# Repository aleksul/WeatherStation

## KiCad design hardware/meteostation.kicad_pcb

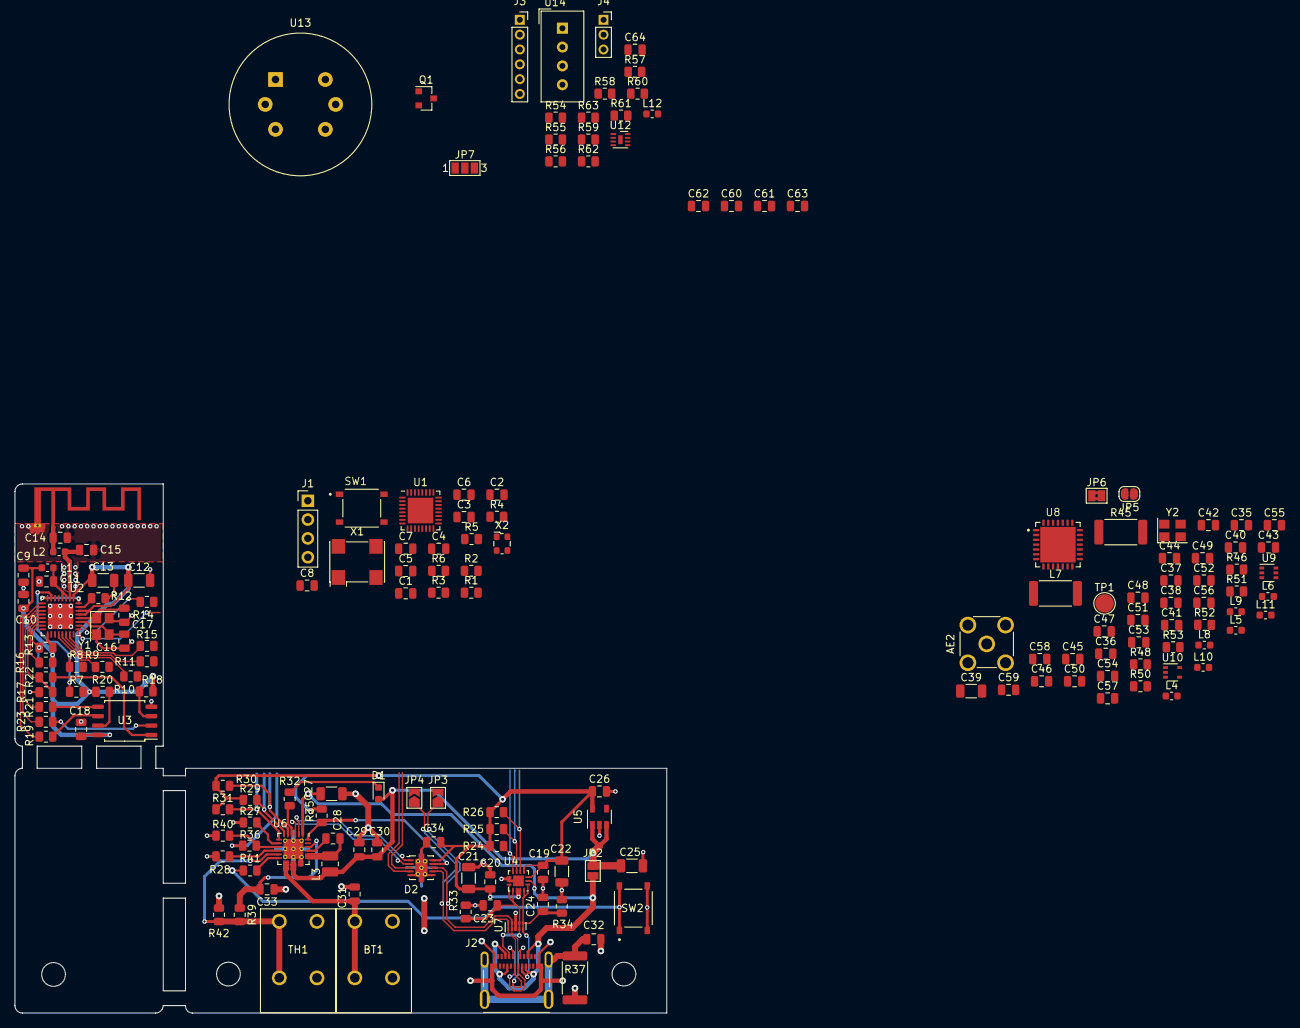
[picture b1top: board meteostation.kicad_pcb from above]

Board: 2 copper layers, 87.9 x 71.3 mm, 172 parts (1 on the bottom side), 115 nets.

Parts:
AE1: Antenna_Chip; Texas_SWRA117D_2.4GHz_Right
AE2: SMA Antenna; SMA_Molex_73251-2200_Horizontal
BT1: Li-Po Battery; DG142R-5.08-02P-14
C1, C2, C5, C6, C7, C8, C10, C11, C18, C19, C20, C32, C34, C40, C41, C42, C54, C55, C64: 100nF; C_0805_2012Metric
C3, C4, C46, C47, C48: 15pF; C_0805_2012Metric
C9, C26, C29, C30, C61, C62, C63: 10uF; C_0805_2012Metric
C12, C13, C21, C22, C25, C27, C39: 1uF; C_1206_3216Metric
C14: 2.4pF; C_0805_2012Metric
C15: 3.0pF; C_0805_2012Metric
C16, C17, C44, C50: 7pF; C_0805_2012Metric
C23, C24: 470pF; C_0805_2012Metric
C28, C43: 47nF; C_0805_2012Metric
C31: 10uF 25V; C_0805_2012Metric
C33, C60: 4.7uF; C_0805_2012Metric
C35, C36, C52, C53, C56: 47pF; C_0805_2012Metric
C37, C38: 2.7pF; C_0805_2012Metric
C45: 18pF; C_0805_2012Metric
C49, C57, C58: 6.8pF; C_0805_2012Metric
C51: 10nF; C_0805_2012Metric
C59: 1nF; C_0805_2012Metric
D1: LED; LED_0603_1608Metric
D2: TS3USB221DCDR; VSON-10-1EP_3x3mm_P0.5mm_EP1.65x2.4mm_ThermalVias
J1: PROG_Conn; PinHeader_1x04_P2.54mm_Vertical
J2: 105450-0101
J3: PM_Sensor; PinSocket_1x06_P2.00mm_Vertical
J4: Anemometer; PinSocket_1x03_P2.00mm_Vertical
JP1: Jumper_PROG; SolderJumper-2_P1.3mm_Open_TrianglePad1.0x1.5mm
JP2: Jumper; SolderJumper-2_P1.3mm_Open_Pad1.0x1.5mm
JP3, JP4: Jumper; SolderJumper-2_P1.3mm_Open_TrianglePad1.0x1.5mm
JP5: Jumper; SolderJumper-2_P1.3mm_Open_RoundedPad1.0x1.5mm
JP6: Jumper; SolderJumper-2_P1.3mm_Bridged2Bar_Pad1.0x1.5mm
JP7: Jumper; SolderJumper-3_P1.3mm_Open_Pad1.0x1.5mm_NumberLabels
L1: 4.3nH; L_0603_1608Metric
L2, L6: 2.2nH; L_0603_1608Metric
L3: 2.2uH; L_1008_2520Metric
L4, L5: 18nH; L_0603_1608Metric
L7: 0R; R_2512_6332Metric
L8, L9, L11: 12nH; L_0603_1608Metric
L10: 33nH; L_0603_1608Metric
L12: 1uH; L_0603_1608Metric
Q1: SI2302; SOT-23
R1, R2, R3, R5, R7, R13, R16, R17, R18, R20, R27, R35, R40, R46, R57, R59, R61, R62, R63: 10K; R_0805_2012Metric
R4, R6, R8, R9, R10, R11, R14, R15, R19, R21, R22, R23, R36, R48, R50, R51, R52, R56, R60: 100R; R_0805_2012Metric
R12: 12K ±1%; R_0805_2012Metric
R24, R25, R26, R29, R30, R31, R41, R54, R55: 4K7; R_0805_2012Metric
R28: 200R; R_0805_2012Metric
R32: 2K2; R_0805_2012Metric
R33, R34, R58: 5K1; R_0805_2012Metric
R37: 330R; R_2512_6332Metric
R39: 5K23; R_0805_2012Metric
R42: 30K1; R_0805_2012Metric
R45: 0R; R_2512_6332Metric
R53: 1K; R_0805_2012Metric
SW1: RESET_BTN; SW_TS-1187A-B-A-B
SW2: Button; SW_TS-1187A-B-A-B
TH1: Thermistor 10K; DG142R-5.08-02P-14
TP1: TestPoint; TestPoint_Pad_D2.5mm
U1: STM32L432KBUx; QFN-32-1EP_5x5mm_P0.5mm_EP3.45x3.45mm
U2: ESP8266EX; QFN-32-1EP_5x5mm_P0.5mm_EP3.45x3.45mm
U3: AT25SF081-SHD-T; SOIC-8_5.23x5.23mm_P1.27mm
U4: FUSB302BMPX; WQFN-14-1EP_2.5x2.5mm_P0.5mm_EP1.45x1.45mm
U5: TLV75533PDBV; SOT-23-5
U6: BQ25895RTW; Texas_S-PWQFN-N24_EP2.7x2.7mm_ThermalVias
U7: TPD4E02B04DQA; USON-10_2.5x1.0mm_P0.5mm
U8: SX1278IMLTRT; QFN65P600X600X100-29N
U9: TPAS179-92LF; SOT-363_SC-70-6
U10: MC74VHC1G14; SOT-353_SC-70-5
U12: HP203B; DFN-8-1EP_2x2mm_P0.5mm_EP0.6x1.2mm
U13: MQ-2; MQ-6
U14: DHT11; Aosong_DHT11_5.5x12.0_P2.54mm
X1: YSO110TR_8MHz_10ppm; Oscillator_SMD_SeikoEpson_SG8002CA-4Pin_7.0x5.0mm
X2: YSO120TK_32.768KHz_10ppm; Oscillator_SMD_ECS_2520MV-xxx-xx-4Pin_2.5x2.0mm
Y1: YSX321SL_26MHz_10ppm; Crystal_SMD_3225-4Pin_3.2x2.5mm
Y2: YSX321SL_32.0MHz_10ppm; Crystal_SMD_3225-4Pin_3.2x2.5mm

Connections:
+3V3: C1.1, C2.1, C6.1, C7.1, C8.1, C9.1, C10.1, C12.1, C13.1, C18.1, C19.1, C20.1, C21.1, C22.1, C26.1, C34.1, C39.1, C40.1, C41.1, C42.1, C43.1, C60.1, C64.1, D2.10, JP7.3, L1.1, R1.1, R2.1, R3.1, R7.2, R13.1, R16.1, R18.2, R20.2, R24.2, R25.2, R26.2, R29.2, R30.2, R31.2, R35.1, R46.1, R54.1, R55.1, R59.1, R62.1, R63.1, U1.1, U1.5, U1.17, U2.1, U2.11, U2.17, U2.29, U2.30, U3.8, U4.3, U4.4, U4.12, U4.13, U5.5, U8.3, U8.14, U8.24, U10.5, U12.3, U12.8, U13.4, U13.6, U14.1, X1.4, X2.4
+5V: C61.1, C62.1, J3.1, JP7.1, U13.2
/Anemometer: J4.3, U1.10
/BOOT0: R5.1, U1.31
/BQ25895_INT: R31.1, U1.27, U6.7
/Charge: R36.2, U1.15
/DHT11: R59.2, U1.11, U14.2
/ESP8266/CHIP_PU: R7.1, R8.1, U2.7
/ESP8266/HSPI_CLK: R19.1, U2.9
/ESP8266/HSPI_CS: R17.2, R22.2, U2.13
/ESP8266/HSPI_MISO: R23.1, U2.10
/ESP8266/HSPI_MOSI: R21.1, U2.12
/ESP8266/RX: R4.1, U2.25
/ESP-LoRa_CS: R9.1, R48.2, U1.14
/ESP_Disable-RF_Mod: JP5.2, R8.2, U1.3
/Enable_5V: R56.2, U1.18
/Enable_MQ2: R60.2, U1.25
/FUSB302_INT: R26.1, U1.26, U4.5
/HSE: C3.1, U1.6, X1.3
/LSE: C4.1, U1.2, X2.3
/MQ2: R58.1, U1.13, U13.1, U13.3
/Power and USB/CC1: C23.1, J2.A5, R33.1, U4.10, U4.11, U7.4, U7.7
/Power and USB/CC2: C24.1, J2.B5, R34.1, U4.1, U4.14, U7.5, U7.6
/Power and USB/ControlSelect: D2.9, R35.2, U6.24
/Power and USB/D+: D2.8, J2.A6, J2.B6, JP3.1, U7.2, U7.9
/Power and USB/D-: D2.7, J2.A7, J2.B7, JP4.1, U7.1, U7.10
/Power and USB/USB_PWR_D+: D2.1, U6.2
/Power and USB/USB_PWR_D-: D2.2, U6.3
/RESET: C5.1, J1.3, R3.2, U1.4
/SCL: R25.1, R30.1, R54.2, U1.19, U4.6, U6.5, U12.5
/SDA: R24.1, R29.1, R55.2, U1.20, U4.7, U6.6, U12.6
/STM_MISO: R11.1, R51.2, U1.12
/STM_MOSI: R15.1, R52.2, U1.28
/STM_RX1-DIO1: R14.1, U1.9, U8.9
/STM_RX2: J3.4, U1.30
/STM_SCK: R10.1, R50.2, U1.7
/STM_TX1-DIO0: R4.2, U1.8, U8.8
/STM_TX2: R6.1, U1.29
/SWCLK: J1.2, U1.24
/SWDIO: J1.1, U1.23
/SX1278/NRESET: R46.2, U8.7
/SX1278/RF1: C36.1, U9.3
/SX1278/RF2: C38.1, C49.1, L9.2, U9.1
/SX1278/RFI: L4.1, L5.1, U8.1
/SX1278/RFO: L6.1, U8.27
/SX1278/RXTX: JP5.1, JP6.2, R53.2, TP1.1
/SX1278/VR_PA: C51.1, C52.1, C53.1, L10.2, U8.25
/SX1278/XTA: C50.1, U8.5, Y2.3
/SX1278/XTB: C44.1, U8.6, Y2.1
/Sensors/PM_RESET: J3.2, R62.2
/Sensors/PM_RX: J3.3, R6.2
/Sensors/PM_SET: J3.5, R63.2
/USB_D+: D2.3, JP3.2, U1.22
/USB_D-: D2.4, JP4.2, U1.21
GND: AE1.2, AE2.2, BT1.2, C1.2, C2.2, C3.2, C4.2, C5.2, C6.2, C7.2, C8.2, C9.2, C10.2, C11.1, C12.2, C13.2, C14.1, C15.1, C16.2, C17.2, C18.2, C19.2, C20.2, C21.2, C22.2, C23.2, C24.2, C25.2, C26.2, C27.2, C29.2, C30.2, C31.2, C32.1, C33.1, C34.2, C39.2, C40.2, C41.2, C42.2, C43.2, C44.2, C46.2, C47.2, C48.2, C49.2, C50.2, C51.2, C52.2, C53.2, C54.1, C55.1, C57.2, C58.2, C59.2, C60.2, C61.2, C62.2, C63.2, C64.2, D2.5, D2.6, D2.11, J1.4, J2.A1, J2.A12, J2.B1, J2.B12, J3.6, J4.2, JP1.2, L5.2, Q1.2, R5.2, R12.2, R17.1, R27.1, R28.2, R33.2, R34.2, R37.1, R40.1, R42.2, R57.2, R58.2, R61.2, SW1.1, SW1.2, SW2.2, TH1.2, U1.16, U1.32, U1.33, U2.33, U3.4, U4.8, U4.9, U4.15, U5.2, U6.17, U6.18, U6.25, U7.3, U7.8, U8.0, U8.15, U8.23, U8.26, U9.2, U10.3, U12.2, U14.4, X1.2, X2.2, Y1.2, Y1.4, Y2.2, Y2.4
unnamed: AE1.1, C14.2, L2.1
unnamed: AE2.1, C57.1, L11.1
unnamed: BT1.1, C31.1, U6.13, U6.14
unnamed: C11.2, L1.2, U2.3, U2.4
unnamed: C15.2, L2.2, U2.2
unnamed: C16.1, U2.27, Y1.3
unnamed: C17.1, U2.28, Y1.1
unnamed: C28.1, L3.1, U6.19, U6.20
unnamed: C28.2, U6.21
unnamed: C32.2, J2.S1, J2.S2, J2.S3, J2.S4, R37.2
unnamed: C33.2, R39.1, U6.22
unnamed: C35.1, R45.2
unnamed: C35.2, L4.2
unnamed: C36.2, R45.1
unnamed: C37.1, C38.2, C48.1, L8.2, L9.1
unnamed: C37.2, C47.1, L7.2, L8.1
unnamed: C45.1, L7.1
unnamed: C45.2, C46.1, L6.2, L10.1
unnamed: C54.2, U8.2
unnamed: C55.2, U8.4
unnamed: C56.1, U9.5
unnamed: C56.2, C58.1, L11.2
unnamed: C59.1, R53.1, U9.4, U10.2
unnamed: D1.1, R32.2
unnamed: J4.1, JP7.2
unnamed: JP1.1, R13.2, U2.15
unnamed: JP6.1, U8.20
unnamed: Q1.1, R60.1, R61.1
unnamed: Q1.3, U13.5
unnamed: R1.2, X1.1
unnamed: R2.2, X2.1
unnamed: R9.2, U2.20
unnamed: R10.2, U2.21
unnamed: R11.2, U2.22
unnamed: R12.1, U2.31
unnamed: R14.2, U2.26
unnamed: R15.2, U2.23
unnamed: R16.2, U2.14
unnamed: R18.1, U3.3
unnamed: R19.2, U3.6
unnamed: R20.1, U3.7
unnamed: R21.2, U3.5
unnamed: R22.1, U3.1
unnamed: R23.2, U3.2
unnamed: R27.2, U6.8
unnamed: R28.1, U6.10
unnamed: R32.1, U6.4
unnamed: R36.1, R40.2, U6.9
unnamed: R39.2, R42.1, TH1.1, U6.11
unnamed: R41.1, SW2.1
unnamed: R41.2, U6.12
unnamed: R48.1, U8.19
unnamed: R50.1, U8.16
unnamed: R51.1, U8.17
unnamed: R52.1, U8.18
unnamed: R56.1, R57.1
unnamed: U2.8, U2.32
unnamed: U9.6, U10.4
VBUS: C27.1, J2.A4, J2.A9, J2.B4, J2.B9, JP2.1, U4.2, U6.1
VCC: C25.1, C29.1, C30.1, C63.1, D1.2, JP2.2, L3.2, L12.1, U5.1, U5.3, U6.15, U6.16

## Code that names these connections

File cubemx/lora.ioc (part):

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Mcu.Name=STM32L432K(B-C)Ux
Mcu.Package=UFQFPN32
Mcu.UserName=STM32L432KBUx
PA0.Mode=HSE-External-Clock-Source-for-LittleOrca
PA0.Signal=RCC_CK_IN
PA1.Mode=Full_Duplex_Master
PA1.Signal=SPI1_SCK
PA10.Mode=I2C
PA10.Signal=I2C1_SDA
PA11.Mode=Device
PA11.Signal=USB_DM
PA12.Mode=Device
PA12.Signal=USB_DP
PA13\ (JTMS-SWDIO).Mode=Serial_Wire
PA13\ (JTMS-SWDIO).Signal=SYS_JTMS-SWDIO
PA14\ (JTCK-SWCLK).Mode=Serial_Wire
PA14\ (JTCK-SWCLK).Signal=SYS_JTCK-SWCLK
PA15\ (JTDI).GPIOParameters=GPIO_Label
PA15\ (JTDI).GPIO_Label=Enable_MQ2
PA15\ (JTDI).Signal=GPIO_Output
PA2.GPIOParameters=GPIO_Label
PA2.GPIO_Label=LORA_DIO0
PA2.Signal=GPIO_Output
PA3.GPIOParameters=GPIO_Label
PA3.GPIO_Label=LORA_DIO1
PA3.Signal=GPIO_Output
PA4.GPIOParameters=GPIO_Label
PA4.GPIO_Label=Anemometer
PA4.Signal=ADCx_IN9
PA5.GPIOParameters=GPIO_Label
PA5.GPIO_Label=DHT11
PA5.Signal=ADCx_IN10
PA6.Mode=Full_Duplex_Master
PA6.Signal=SPI1_MISO
PA7.GPIOParameters=GPIO_Label
PA7.GPIO_Label=MQ2
PA7.Signal=ADCx_IN12
PA8.GPIOParameters=GPIO_Label
PA8.GPIO_Label=Enable_5V
PA8.Signal=GPIO_Output
PA9.Mode=I2C
PA9.Signal=I2C1_SCL
PB0.GPIOParameters=GPIO_Label
PB0.GPIO_Label=LORA_CS
PB0.Signal=GPIO_Output
PB1.GPIOParameters=GPIO_Label
PB1.GPIO_Label=Charge
PB1.Signal=GPIO_Output
PB3\ (JTDO-TRACESWO).GPIOParameters=GPIO_Label
PB3\ (JTDO-TRACESWO).GPIO_Label=FUSB302_INT
PB3\ (JTDO-TRACESWO).Signal=GPXTI3
PB4\ (NJTRST).GPIOParameters=GPIO_Label
PB4\ (NJTRST).GPIO_Label=BQ25895_INT
PB4\ (NJTRST).Signal=GPXTI4
PB5.Mode=Full_Duplex_Master
PB5.Signal=SPI1_MOSI
PB6.Mode=Asynchronous
PB6.Signal=USART1_TX
PB7.Mode=Asynchronous
PB7.Signal=USART1_RX
PC14-OSC32_IN\ (PC14).Mode=LSE-External-Clock-Source
PC14-OSC32_IN\ (PC14).Signal=RCC_OSC32_IN
PC15-OSC32_OUT\ (PC15).GPIOParameters=GPIO_Label
PC15-OSC32_OUT\ (PC15).GPIO_Label=RF_MOD
PC15-OSC32_OUT\ (PC15).Signal=GPIO_Output
RCC.HSE_VALUE=8000000
RCC.SYSCLKFreq_VALUE=32000000
RCC.SYSCLKSource=RCC_SYSCLKSOURCE_PLLCLK
board=custom

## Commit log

2021-02-22 Init commit
2021-02-22 Add initial kicad project, including: - atmega328pb-au - esp8266
2021-02-23 Changed esp8266 chip_en
2021-02-23 Finished esp8266 schematics
2021-02-24 Add dc-dc converters
2021-02-27 Changed atmega power to 3.3v instead of 5v Added type-c connector
2021-02-28 Add LICENSE
2021-02-28 Finished routing USB type-c and battery charging IC
2021-03-09 Add cubemx project Changed MCU and PD scheme
2021-03-10 Changed flash for esp8266 Added stm32 schematic
2021-03-13 Changing power circuit again
2021-03-14 Finished power schematics
2021-03-23 All sensors + most of MCU done
2021-03-26 Finished main list
2021-04-18 Finished sx1278 schematic
2021-04-21 Select crystals, add HSE for stm32 and fixed some bits
2021-04-25 Annotation complete
2021-04-27 Finish adding footprints
2021-04-27 Optimazed labels
2021-04-28 Update cubemx files
2021-04-30 Change 0Rto solder jumpers Add 3d model for bq25895 Fix button pcb model Start power part of pcb
2021-04-30 Power part 1/2 done
2021-05-22 Finished power PCB part
2021-10-28 Finish esp8266 PCB part
